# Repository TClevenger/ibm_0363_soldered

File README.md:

# IBM_0363_soldered

An alternative to the unobtainium/exhorbitantly expensive IBM 0363 (45H2433) port box for the Integrated Netfinity PC on the AS/400 Model 150 and probably others.  This breaks out the PS/2 keyboard and mouse ports from the MDR-40 mini-delta connector on the back of the Netfinity card set.  

This board is tested to fit CUI MD-60S Mini-DIN ports and uses any four-pair cable to connect to a 3M 10140-3000PE "solder cup" style connector.  Gerbers were made using JLCPCB template.

Current release is V1R1 (2026-04-30)
* Expanded pad size, added header vias, cleaned up silkscreen markings, narrowed strain relief holes
* Added LICENSE file

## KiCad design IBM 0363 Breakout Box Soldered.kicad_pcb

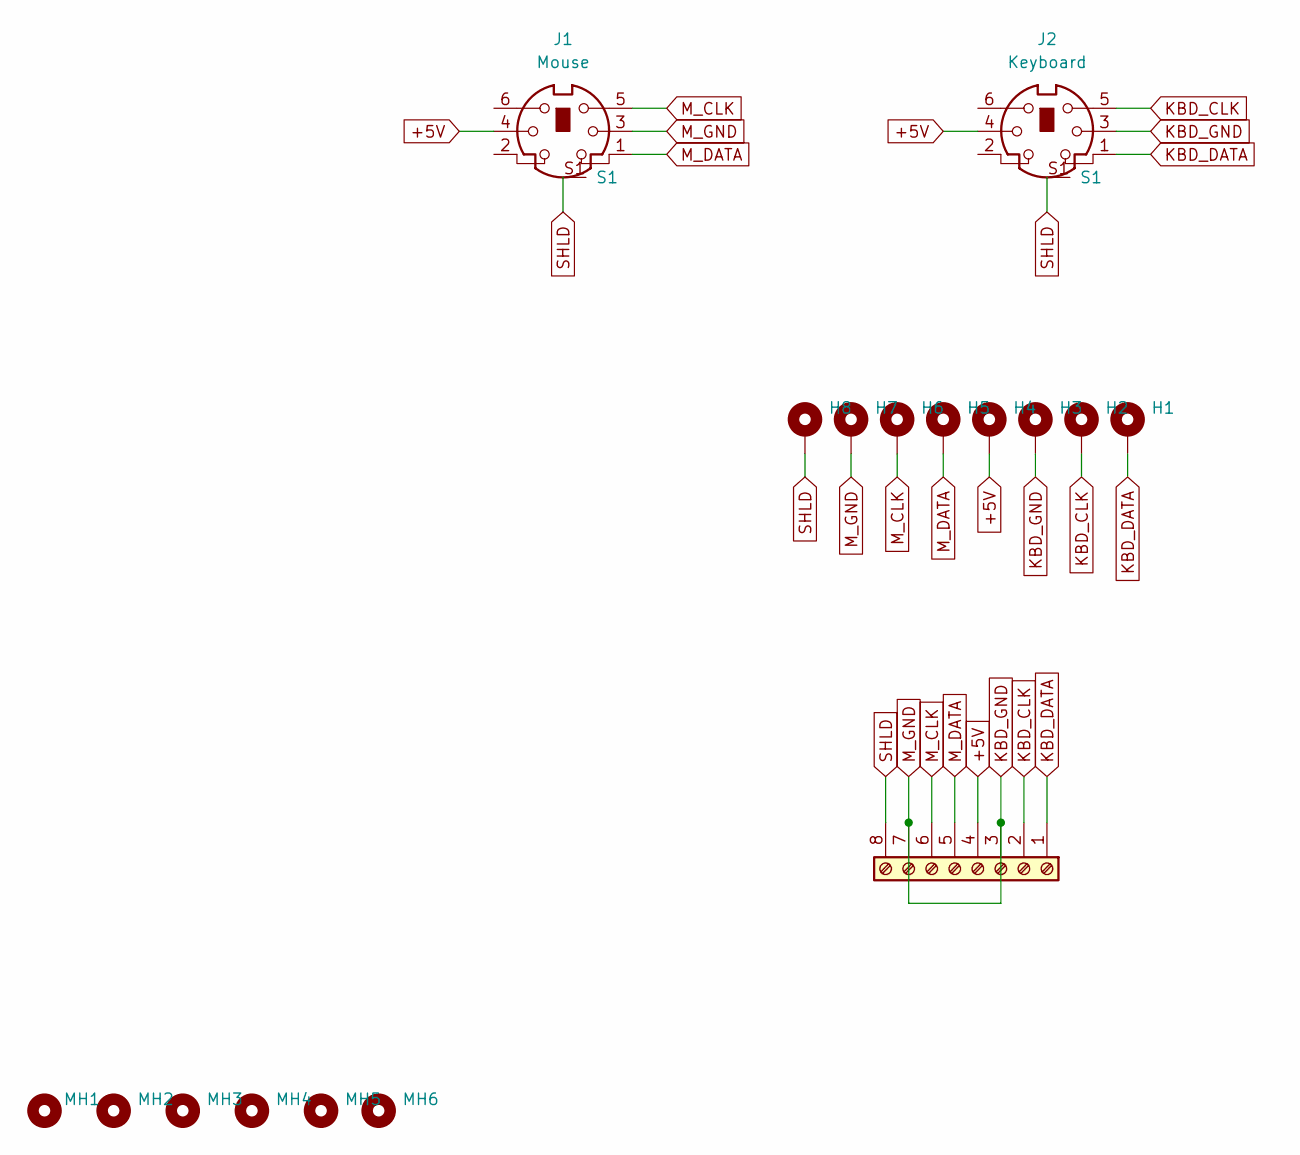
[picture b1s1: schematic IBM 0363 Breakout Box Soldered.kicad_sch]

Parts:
H1: MountingHole_Pad; SolderWirePad_1x01_SMD_2.5x5mm_P1
H2, H3, H4, H5, H6, H7, H8: MountingHole_Pad; SolderWirePad_1x01_SMD_1.5x3mm_P1
J1: Mouse; CUI_MD-60S
J2: Keyboard; CUI_MD-60S
J4: Screw_Terminal_01x08; PinHeader_1x08_P2.54mm_Horizontal
MH1, MH2, MH3, MH4, MH5, MH6: MountingHole; MountingHole_3.2mm_M3

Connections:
+5V: H4.1, J1.4, J2.4, J4.4
KBD_CLK: H2.1, J2.5, J4.2
KBD_DATA: H1.1, J2.1, J4.1
KBD_GND: H3.1, H7.1, J1.3, J2.3, J4.3, J4.7
M_CLK: H6.1, J1.5, J4.6
M_DATA: H5.1, J1.1, J4.5
SHLD: H8.1, J1.S1, J2.S1, J4.8

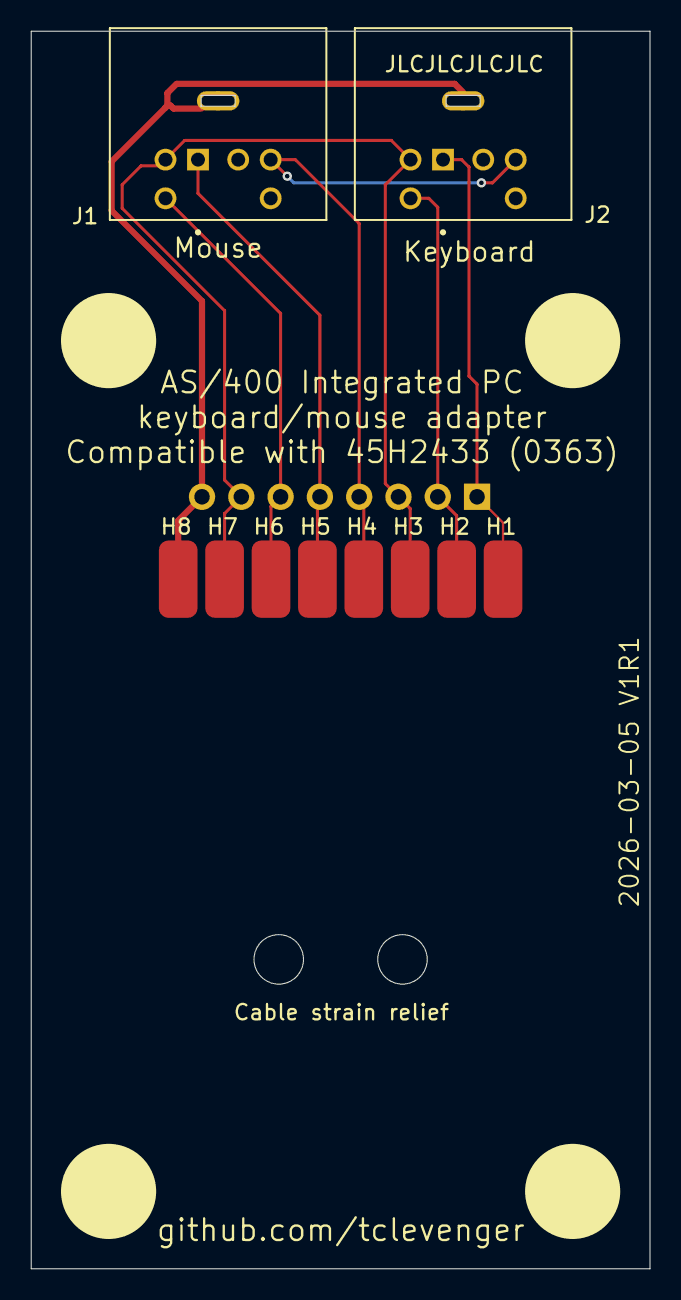
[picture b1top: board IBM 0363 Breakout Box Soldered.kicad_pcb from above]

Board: 2 copper layers, 40.0 x 80.0 mm, 17 parts (1 on the bottom side), 7 nets.

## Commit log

2026-04-30 Initial push
2026-04-30 V1R1 updates
